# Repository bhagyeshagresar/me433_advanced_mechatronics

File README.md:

# ME433 Advanced Mechatronics Repository Spring 2022

# Topics covered:
1) UART
2) I2C
3) SPI
4) IMU
5) Image Processing
6) OLED Display programming
7) Neopixel BitBanging

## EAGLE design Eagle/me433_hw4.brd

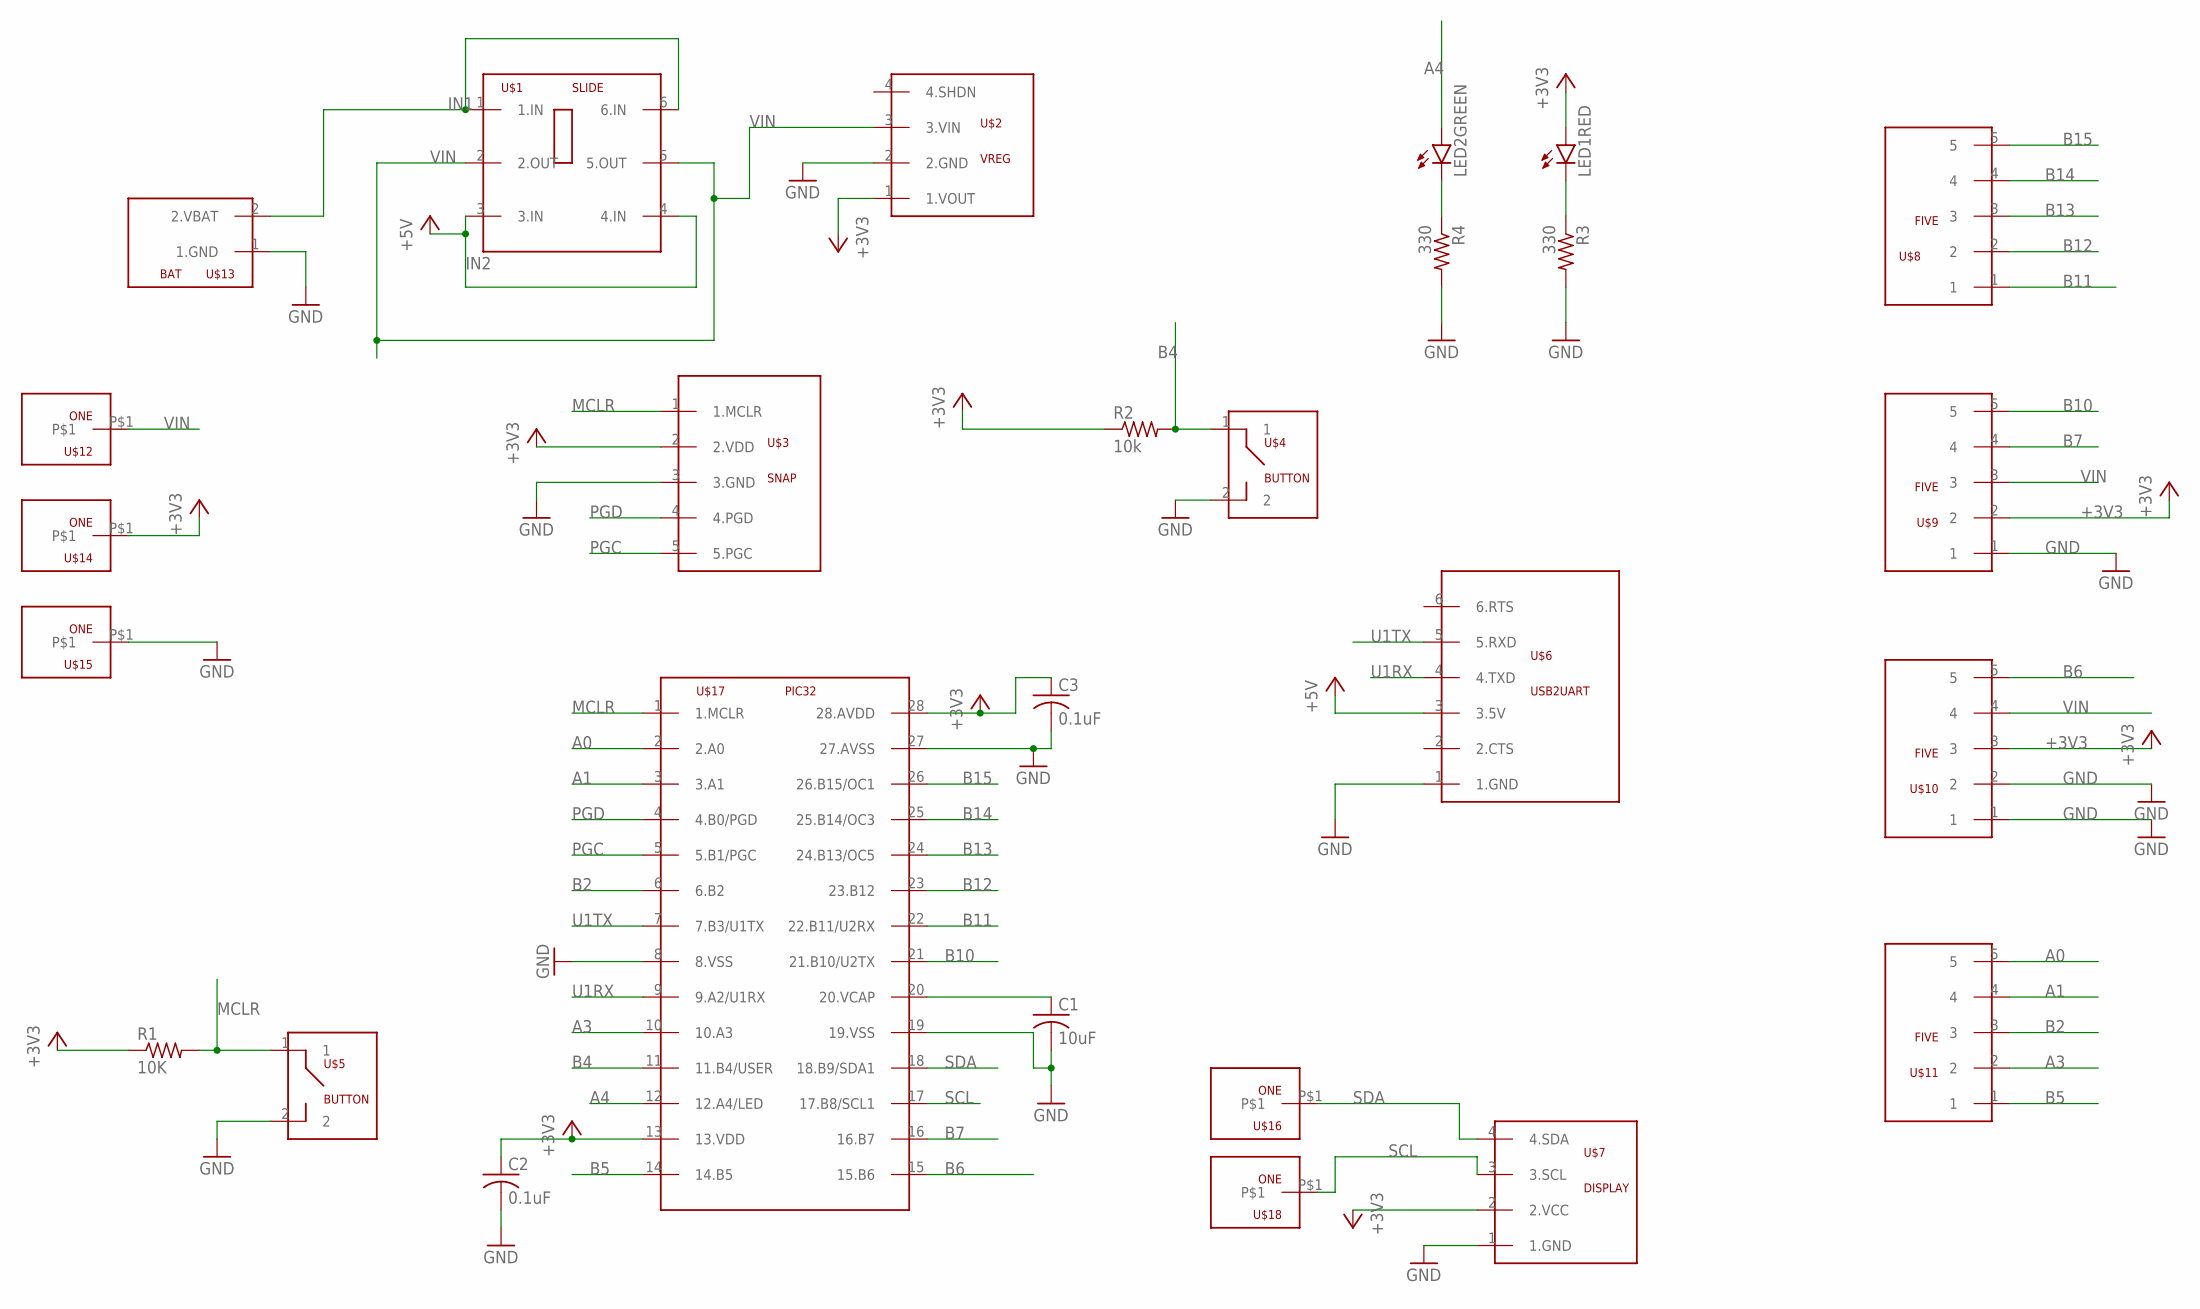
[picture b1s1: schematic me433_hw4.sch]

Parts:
C1: 10uF; C025-024X044
C2, C3: 0.1uF; C025-024X044
LED1RED, LED2GREEN: LED3MM
R1: 10K; 0204/5
R2: 10k; 0204/5
R3, R4: 330; 0204/5
U$1: SLIDE
U$2: VREG
U$3: SNAP
U$4, U$5: BUTTON
U$6: USB2UART
U$7: DISPLAY
U$8, U$9, U$10, U$11: FIVE
U$12, U$14, U$15, U$16, U$18: ONE
U$13: BAT
U$17: PIC32; DIL28-3

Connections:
+3V3: C2.1, C3.1, LED1RED.A, R1.1, R2.1, U$2.1 (1.VOUT), U$3.2 (2.VDD), U$7.2 (2.VCC), U$9.2, U$10.3, U$14.P$1, U$17.13 (13.VDD), U$17.28 (28.AVDD)
+5V: U$6.3 (3.5V)
A0: U$11.5, U$17.2 (2.A0)
A1: U$11.4, U$17.3 (3.A1)
A3: U$11.2, U$17.10 (10.A3)
A4: LED2GREEN.A, U$17.12 (12.A4/LED)
B2: U$11.3, U$17.6 (6.B2)
B4: R2.2, U$4.1, U$17.11 (11.B4/USER)
B5: U$11.1, U$17.14 (14.B5)
B6: U$10.5, U$17.15 (15.B6)
B7: U$9.4, U$17.16 (16.B7)
B10: U$9.5, U$17.21 (21.B10/U2TX)
B11: U$8.1, U$17.22 (22.B11/U2RX)
B12: U$8.2, U$17.23 (23.B12)
B13: U$8.3, U$17.24 (24.B13/OC5)
B14: U$8.4, U$17.25 (25.B14/OC3)
B15: U$8.5, U$17.26 (26.B15/OC1)
GND: C1.2, C2.2, C3.2, R3.2, R4.2, U$2.2 (2.GND), U$3.3 (3.GND), U$4.2, U$5.2, U$6.1 (1.GND), U$7.1 (1.GND), U$9.1, U$10.1, U$10.2, U$13.1 (1.GND), U$15.P$1, U$17.8 (8.VSS), U$17.19 (19.VSS), U$17.27 (27.AVSS)
IN1: U$1.1 (1.IN), U$1.6 (6.IN), U$13.2 (2.VBAT)
IN2: U$1.3 (3.IN), U$1.4 (4.IN)
MCLR: R1.2, U$3.1 (1.MCLR), U$5.1, U$17.1 (1.MCLR)
unnamed: LED2GREEN.K (C), R4.1
unnamed: LED1RED.K (C), R3.1
unnamed: C1.1, U$17.20 (20.VCAP)
PGC: U$3.5 (5.PGC), U$17.5 (5.B1/PGC)
PGD: U$3.4 (4.PGD), U$17.4 (4.B0/PGD)
SCL: U$7.3 (3.SCL), U$17.17 (17.B8/SCL1), U$18.P$1
SDA: U$7.4 (4.SDA), U$16.P$1, U$17.18 (18.B9/SDA1)
U1RX: U$6.4 (4.TXD), U$17.9 (9.A2/U1RX)
U1TX: U$6.5 (5.RXD), U$17.7 (7.B3/U1TX)
VIN: U$1.2 (2.OUT), U$1.5 (5.OUT), U$2.3 (3.VIN), U$9.3, U$10.4, U$12.P$1

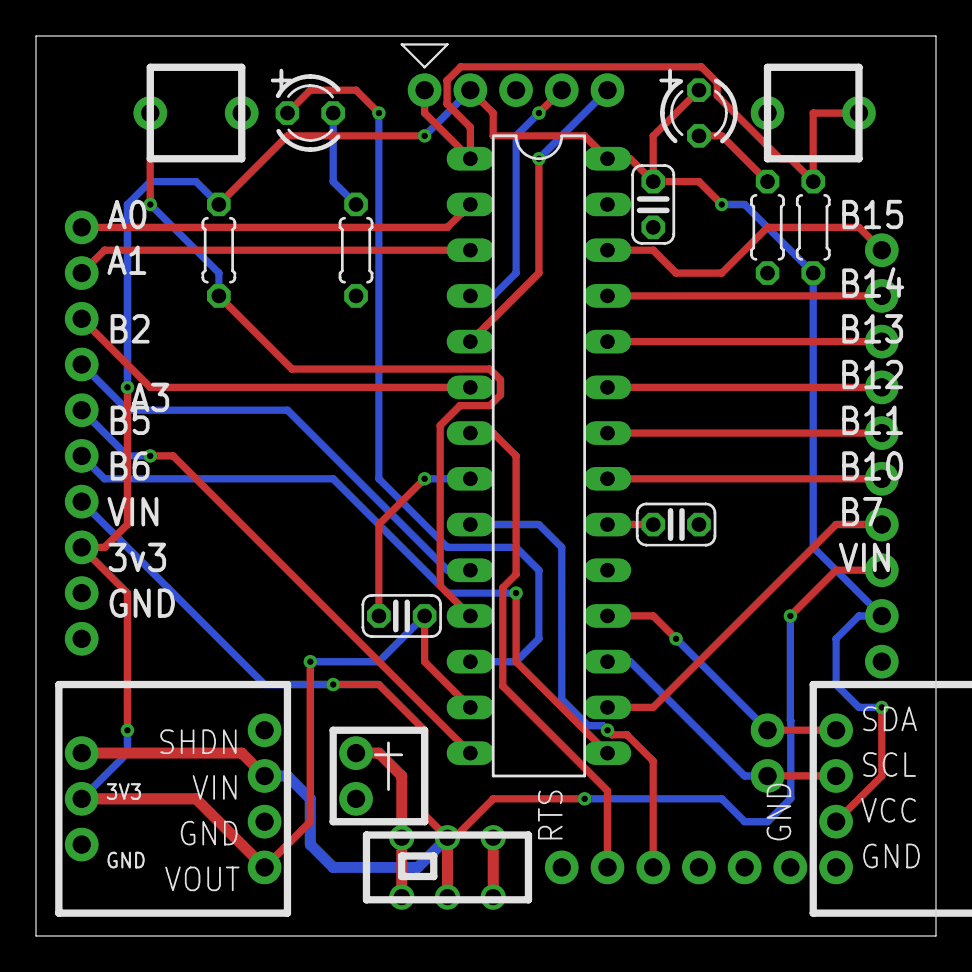
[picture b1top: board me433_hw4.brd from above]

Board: 2 copper layers, 50.0 x 50.0 mm, 27 parts (0 on the bottom side), 30 nets.

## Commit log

2022-03-30 second commit
2022-03-30 third commit
2022-03-30 fourth commit
2022-04-05 added hw2
2022-04-07 added hw3
2022-04-27 added hw5
2022-04-30 finished hw6
2022-05-06 finished hw8
2022-05-13 finished hw7 and hw9
2022-05-27 finished hw10
2022-05-29 finished hw11
2022-06-08 completed hw4
2022-06-09 added hw12
2022-09-09 changed file names
2022-09-09 changed filenames
